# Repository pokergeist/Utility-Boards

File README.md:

# Utility-Boards
Printed curcuit boards designs and associated code for hobby and task related PCBs.

### [Power Alert](Power_Alert/README.md)

An Adafruit Itsy Bitsy powered board that alarms when the power goes out. Extended with an I2C Qwiic connector and pin access for projects that could use batter power (with charging) or big LED or Piezo speaker.

### Pending

I created a few printed circuit boards to perform some simple tasks. Pending uploads:
  * Lighting - using motion sensing to control 12V LED strips (single-color or RGB). Used for under-counter task lighting (color fades to full white) and walkway lighting (on/off).
  * Power Alert - generate an alert (flashing LED and Piezo speaker) when USB or 5V power to the board is lost. It continues to blink after power is restored as a notification. A Li-Po battery provides backup power and is recharged by the board when power is restored.
  * Heater control - string multiple temperature sensors together with phone wire to control a heater. Used in outbuildings to prevent plumbing and fixtures from freezing.

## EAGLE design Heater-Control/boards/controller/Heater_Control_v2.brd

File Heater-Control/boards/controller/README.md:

# Heater Controller Board

## Introduction

This project uses a microcontroller to read a chain of Dallas Semiconductor DS18B20 1-Wire temperature sensors. When any of the sensors reads too low an electric heater is turned on via a "IOT" Power Strip which has a low voltage trigger input (not some Wi-Fi silliness).

The sensors boards are connected together with cheap phone wire cords with RJ-11 connectors on the ends. The control line to the power strip connects via a JST XH 2-pin connector to the strip's screw terminal block, which is removable for easier connection.

The sensor boards have been used with an Arduino Uno and protoboard shield to prevent plumbing and fixtures in an outbuilding from freezing for a few seasons now. This is the next generation build that uses a custom (but simple) circuit board with a smaller enclosure, simpler wiring, and a display.

## Status

|    Date    | Status                                                       |
| :--------: | ------------------------------------------------------------ |
| 2022-24-23 | Added strong pull-up MOSFET and changed pull-up resistor.    |
| 2022-12-18 | Adding a strong pull-up for the DQ line as stability problems have been encountered. |
| 2022-12-02 | First check-in. Gerber and software files pending.           |

**2022-12-23** Reliability Issues have been resolved by reducing the pullup-up resistor value to 3.3k to maintain 1mA of current. The strong pull-up MOSFET didn't resolve the issue, but won't hurt for longer runs, and is deemed a required component in the DS18B20 datasheet. The MOSFET is turned on to sort-of fast charge the sensors before certain operations.

**2022-12-18** One unit has worked fine, the other will either not recognize connected sensors, or the sensors do not stay on-line. The driver supports a strong pull-up provided by a P-channel MOSFET driven by a second GPIO line.

Moving from a 5V MCU to a 3.3V one has probably exposed a lurking problem if the datasheet is any indication.

## Parts List

| Part                        |                            Part #                            |     Quantity      |       Price @q1       | Notes                                                        |
| --------------------------- | :----------------------------------------------------------: | :---------------: | :-------------------: | ------------------------------------------------------------ |
| Microcontroller             | Adafruit QT Py SAMD21 (#[4600](https://www.adafruit.com/product/4600)) [D-K](https://www.digikey.com/short/z7fjv1m0) |         1         |         $7.50         | Available on Digi-Key too.                                   |
| P-Ch MOSFET                 | Microchip [TP2104N3-G](https://www.digikey.com/short/nzjn4r47) |         1         |         $0.74         |                                                              |
| RJ-11 Jack                  |       [43860](https://www.digikey.com/short/1ht3wp4m)        |      1 or 2       |         $1.15         | Combine w/ sensor boards for pricing.                        |
| JST XH-2                    |  [S2B-XH-A(LF)(SN)](https://www.digikey.com/short/hw1pfpn8)  |         1         |         $0.16         |                                                              |
| 3.3kΩ 1206 resistor         | Stackpole [RMCF1206JT4K70](https://www.digikey.com/short/4qf3n4vb) |         1         |         $0.10         | (10) @ $0.025 each                                           |
| 100Ω 1206 resistor          | Stackpole [RMCF1206JT100R](https://www.digikey.com/short/2cb7z251) |         1         |         $0.10         | (10) @ $0.025 each                                           |
| OLED display                |                   SSD-1306 128x32 4-lines                    |         1         |           ?           | Amazon or eBay                                               |
| Qwiic/SQT cable             |                 4-conductor w/ JST connector                 |         1         |           ?           | Amazon or eBay                                               |
| "IOT" Power Strip           |   Adafruit #[2935](https://www.adafruit.com/product/2935)    |         1         |        $34.95         |                                                              |
| PCB                         |           Zipped Gerber files for JLCPCB or PCBWay           |         1         | (5) for $2 + shipping | Shipping speed is the biggest cost factor.                   |
| 4-conductor telephone cable |                          RJ-11 6p4c                          | 1 for each sensor |           ?           | Must be 4-conductor in concentric pairs. The outer two positions of a 6p4c connector are not used. |

## Component Functions

The  microcontroller reads the sensors and controls the power strip. It also displays information to the optional OLED display and/or LED/Neopixel.

The Molex RJ-11 jack connects to the sensor line via 4-conductor telephone cables.

The JST XH 2-pin connector connects to the power strip to turn it on and off.

The pull-up resistor pulls the DQ 1-wire data line up to 3V3. The MOSFET provides a strong pullup-up to 3V3 prior to certain operations. The driver is responsible for not setting the DQ line LOW at the same time.

The optional 128x32 pixel 4-line I2C OLED display show individual and minimum temperatures per read cycle, the lowest long-term temp, heater status, and total heater run-time. Or whatever you care to add to the code.

The Qwiic/STEMMA QT cable provide power and data to the OLED display. Order a short cable and solder one end to the display, and plug the connector end into the QT Py micro.

## Board Images

## Wiring

Power is provided via a USB-C cable to the QT Py micro. The small heater is powered from the power strip which also power the USB-C cable via one of the "Always On" outlets.

The OLED display is controlled and powered via the Qwiic/STEMMA QT I2C connector on the QT Py micro.

When using cheap 4-conductor phone line line you'll find that the the connectors are often crimped such that the pin order is reversed from end-to-end. This is not an issue for phone equipment using the outer and inner concentric pairs. You do have to make sure that it's a 4-conductor cable and not just 2 conductors for the center pair.

The DS18B20 supports parasitic power. The three terminals are:

* Vdd - power
* DQ - data
* GND - ground

With power provided via the pulled-up DQ line, and the Vdd pin grounded, the IC operates on parasitic power. I use both leads of the inner pair for data/power line DQ and the outer pair for ground.

## The Enclosure

The SCAD and .stl files for a simple enclosure are provided. (still tweaking the design)

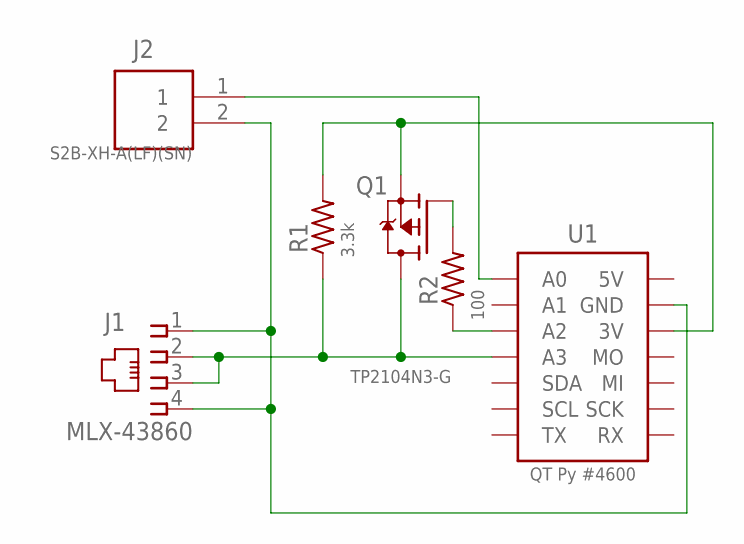
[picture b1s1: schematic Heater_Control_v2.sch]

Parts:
J1: MLX-43860
J2: S2B-XH-A(LF)(SN); HDR-02/RA
Q1: TP2104N3-G; TO92-
R1: 3.3k; R1206
R2: 100; R1206
U1: QT Py #4600; QT_PY-TH

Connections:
3V3: Q1.1 (S), R1.2, U1.3V3@1 (3V), U1.3V3@2 (3V)
5V: U1.5V@1 (5V), U1.5V@2 (5V)
DATA-1WIRE: J1.2, J1.3, Q1.3 (D), R1.1, U1.A3@1 (A3), U1.A3@2 (A3)
GATE: Q1.2 (G), R2.2
GND: J1.1, J1.4, J2.2, U1.GND@1 (GND), U1.GND@2 (GND)
PWR: J2.1, U1.A0@1 (A0), U1.A0@2 (A0)
SPU_GATE: R2.1, U1.A2@1 (A2), U1.A2@2 (A2)

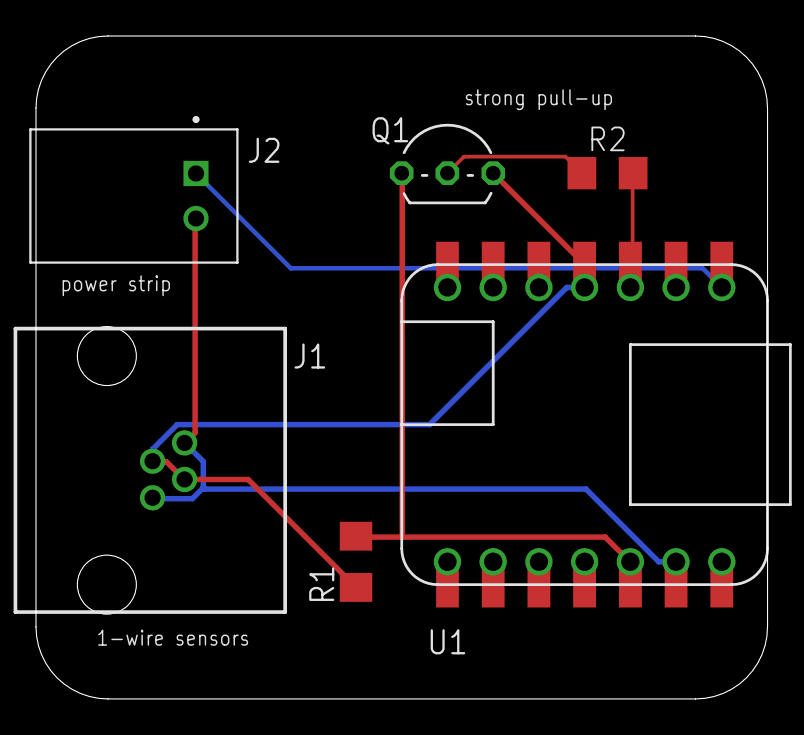
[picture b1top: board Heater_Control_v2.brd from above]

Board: 2 copper layers, 40.6 x 36.8 mm, 6 parts (0 on the bottom side), 7 nets.

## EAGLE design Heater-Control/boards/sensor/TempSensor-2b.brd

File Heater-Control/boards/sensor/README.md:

# Heater Sensor Board

## Intro

This project uses a microcontroller to read a chain of Dallas Semiconductor DS18x20 1-Wire temperature sensors. When any of the sensors reads too low an electric heater is turned on via a "IOT" Power Strip.

The sensors boards are connected together with cheap phone wire cords with RJ-11 connectors on the ends. The control line to the power strip connects via a JST XH 2-pin connector to the strip's screw terminal block, which is removable for easier connection.

The sensor boards have been used with an Arduino Uno and protoboard shield to prevent plumbing and fixtures in an outbuilding from freezing for a few seasons now. This is the next generation build that uses a custom (but simple) circuit board with a smaller enclosure, simpler wiring, and a display.

## Status

|    Date    | Status                                           |
| :--------: | ------------------------------------------------ |
| 2022-12-03 | Redesigned Sensor board. Ordered (5) 3x3 panels. |
| 2022-12-02 | First check-in. Gerber files are pending.        |

As fate would have it I need more sensor boards so I revised the sensor part schematic then the board. Obsolete parts were removed. Mounting options were revised.

## Parts List

|        Item        |                         Part #                          | Quantity |                     Price @q10                      | Notes                                      |
| :----------------: | :-----------------------------------------------------: | :------: | :-------------------------------------------------: | ------------------------------------------ |
| Temperature Sensor | [1-Wire Search](https://www.digikey.com/short/5w14dwnw) |    1     |                       $6.413                        | See below.                                 |
|     RJ-11 Jack     |     [43860](https://www.digikey.com/short/1ht3wp4m)     |  1 or 2  |                       $0.949                        |                                            |
|        PCB         |        Zipped Gerber files for JLCPCB or PCBWay         |    5+    | (5) for $2 + shipping<br/>(45) for $7.30 + shipping | Shipping speed is the biggest cost factor. |

**Notes on the PCB:**

The new PCB is small enough to be panelized where multiple boards are made on one panel and milled so that they snap apart. The standard minimum order is (5) 100x100mm (or smaller) boards for $2.00 plus shipping. With panelized boards you get (5) panels for a few dollars more. With (9) boards per panel you can easily get (45) individual boards for a reasonable price.

**Notes regarding the temperature sensor:**

The old Dallas Semi DS18x20 1-Wire Temperature sensor has fallen out of favor and is becoming increasingly rare and costly. Items to consider regarding the Digi-Key search results linked to above:

* The MAX31820  sensors are cheaper but the DS18(b)20/20 has better accuracy from +10°C to -10°C.
* These offer 11 or 12-bit precision - I'm only using 10-bits.

You can probably source the DS18B20 sensors cheaper on eBay or [AllElectronics.com](https://www.allelectronics.com/item/ds18b20/digital-temperature-sensor/1.html).

After my stock of DS18B20s runs out I'll probably switch to a cheap I2C-based chip, but that would ruin my scheme of using cheap phone cables without regard to their connector polarity (which was a pain to check on every single cable).

## Wiring

When using cheap 4-conductor phone line line you'll find that the the connectors are often crimped such that the pin order is reversed from end-to-end. This is not an issue for telephone equipment using the outer and inner concentric pairs. You do have to make sure that it's a 4-conductor cable and not just 2 conductors using only the center pair.

The DS18x20 supports parasitic power. The three terminals are:

* Vdd - power
* DQ - data
* GND - ground

With power provided via the pulled-up DQ line, and the Vdd pin grounded, the IC operates on parasitic power. I use both leads of the inner pair for data/power line DQ and the outer pair for ground.

## Mounting Options

The new board offers multiple mounting options:

* There are notches for mounting with a cable tie.
* Two M3 holes are provided at the center and corner.
* A sensor can be soldered on either side (or even both sides if desired).

## Schematic

The schematic shows two locations for the sensor, U1T and B for top and bottom. This gives the option of installing a sensor **on either the top or bottom side** depending on how the board is mounted and the best location for the sensor. You could install two sensors, but that is not the intention.

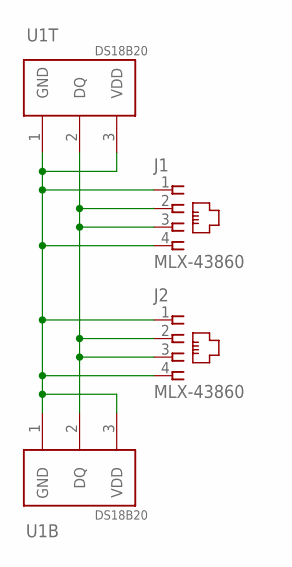
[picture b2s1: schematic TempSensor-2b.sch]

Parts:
J1, J2: MLX-43860
U1B, U1T: DS18B20; TO92-

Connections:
1W: J1.2, J1.3, J2.2, J2.3, U1B.2 (DQ), U1T.2 (DQ)
GND: J1.1, J1.4, J2.1, J2.4, U1B.1 (GND), U1B.3 (VDD), U1T.1 (GND), U1T.3 (VDD)

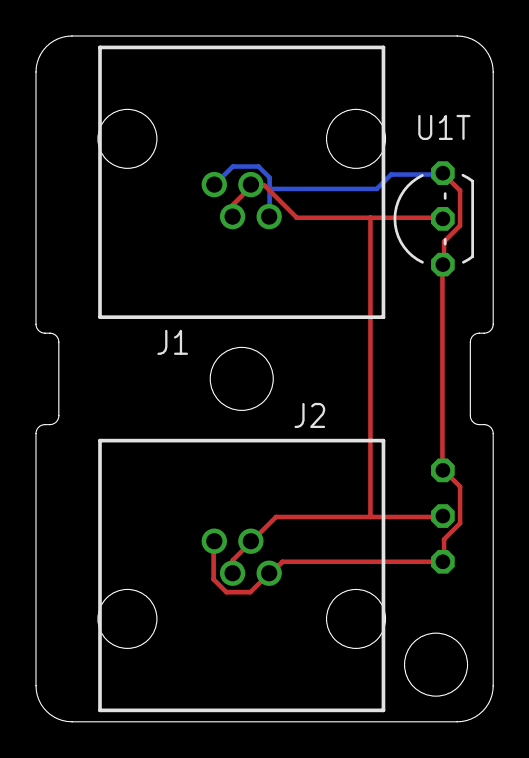
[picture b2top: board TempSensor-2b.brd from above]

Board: 2 copper layers, 25.4 x 38.1 mm, 4 parts (1 on the bottom side), 2 nets.

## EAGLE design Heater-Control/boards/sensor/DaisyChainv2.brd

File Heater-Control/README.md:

# Heater Control Project

## Intro

This project uses a microcontroller to read a chain of Dallas Semiconductor DS18B20 1-Wire temperature sensors. When any of the sensors reads too low an electric heater is turned on via a "IOT" Power Strip.

The sensors boards are connected together with cheap phone wire cords with RJ-11 connectors on the ends. The control line to the power strip connects via a JST XH 2-pin connector to the strip's screw terminal block, which is removable for easier connection.

The sensor boards have been used with an Arduino Uno and protoboard shield to prevent plumbing and fixtures in an outbuilding from freezing for a few seasons now. This is the next generation build that uses a custom (but simple) circuit board with a smaller enclosure, simpler wiring, and a display.

## Status

|    Date    | Status                                                       |
| :--------: | ------------------------------------------------------------ |
| 2022-12-24 | Updated control board files.                                 |
| 2022-12-23 | Changed out the 4.7kΩ pull-up resistor for a 3.3kΩ one and finished the installation. |
| 2022-12-18 | Adding a hard pull-up for the DQ line as stability problems have been encountered. |
| 2022-12-02 | First check-in. Gerber, enclosure, and software files pending. |

**2022-12-23** I added the p-channel MOSFET for the strong pull-up. That didn't improve anything at all. I finally swapped out the 4.7kΩ pull-up resistor for a 3.3kΩ one since the voltage had changed from 5V to 3.3V. After that the project started working reliably with and without the strong pull-up function. I'll be adding the strong pull-up components to the board design - it will likely help with longer sensor runs.

**2022-12-18** One unit has worked fine, the other will either not recognize connected sensors, or the sensors do not stay on-line. The driver supports a hard pull-up provided by a P-channel MOSFET driven by a second GPIO line.

Moving from a 5V MCU to a 3.3V one has probably exposed a lurking problem if the datasheet is any indication.

## The Boards

### The Controller Board

The controller board hosts:

*  an Adafruit QT Py SAMD21 (#4600) microcontroller
* a Molex RJ-11 jack for connecting to the sensor line
* a JST XH 2-pin connector for controlling the power strip
* a pull-up resistor to pull the DQ 1-wire data line up to 3V3
* an optional 128x32 pixel 4-line I2C OLED display.

### The Sensor Board

Sensor board components:

* A Dallas Semi DS18B20 1-Wire Temperature sensor
* a Molex RJ-11 Jack
* Deprecated components:
  * a JST XH 3-pin for connecting to the old controller (now vacant)
  * a 4.7kΩ pull-up resistor for use with the old controller (now vacant)

## Wiring

When using cheap 4-conductor phone line line you'll find that the the connectors are often crimped such that the pin order is reversed from end-to-end. This is not an issue for phone equipment using the outer and inner concentric pairs. You do have to make sure that it's a 4-conductor cable and not just 2 conductors for the center pair.

The DS18x20 supports parasitic power. The three terminals are:

* Vdd - power
* DQ - data
* GND - ground

With power provided via the pulled-up DQ line, and the Vdd pin grounded, the IC operates on parasitic power. I use both leads of the inner pair for data/power line DQ and the outer pair for ground.

Power is provided via a USB-C cable to the QT Py micro. The small heater is powered from the power strip which also power the USB-C cable via one of the "Always On" outlets.

The OLED display is controlled and powered via the Qwiic/STEMMA QT I2C connector on the QT Py micro.

## The Enclosure

The SCAD and .stl files for a simple enclosure are provided. (still tweaking the design)

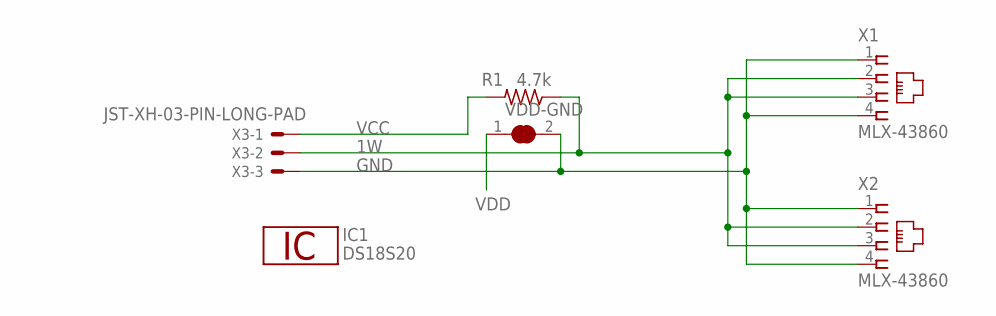
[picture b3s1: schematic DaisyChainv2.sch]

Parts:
IC1: DS18S20; TO92-
R1: 4.7k; 0207/10
VDD-GND: SJW-SHORTED
X1, X2: MLX-43860
X3: JST-XH-03-PIN-LONG-PAD; JST-XH-03-PACKAGE-LONG-PAD

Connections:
1W: IC1.2 (1W), R1.1, X1.2, X1.3, X2.2, X2.3, X3.2
GND: IC1.1 (GND), VDD-GND.2, X1.1, X1.4, X2.1, X2.4, X3.3
VCC: R1.2, X3.1
VDD: IC1.3 (VDD), VDD-GND.1

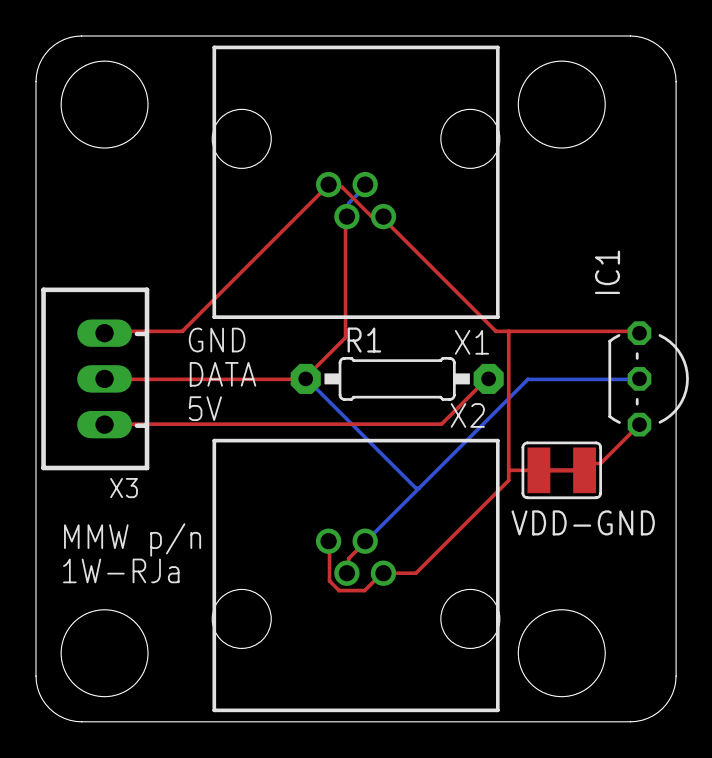
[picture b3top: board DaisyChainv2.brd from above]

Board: 2 copper layers, 35.6 x 38.1 mm, 6 parts (0 on the bottom side), 4 nets.

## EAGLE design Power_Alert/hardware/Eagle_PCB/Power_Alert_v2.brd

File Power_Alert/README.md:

# Power Alert

A board that alerts you to a power loss. Maybe more.

### Overview

This board has some general utility given that it has:

+ a big, bright LED
+ a Piezo speaker
+ a battery connector for a lithium battery - Li-ion or Li-po pouch cell
+ a charging IC for the lithium battery (4.2V).

To that end it has been extended for alternate uses. It provides:

* a Qwiic/STEMMA QT I2C connector providing GND, V+, SDA and SCL for connection to sensors, displays, ...
* exposed Itsy Bitsy MCU pins
  * GPIO: A0, A1,  A2, D4, D6, D8
  * SPI: MOSI, MISO, SCLK
  * Power: Vdd, GND

### Board Components

An export of my [Digi-Key](https://www.digikey.com/) project list is located in the hardware folder. Two things to be aware of:

1. Two piezo elements are listed. The [larger](https://www.digikey.com/en/products/detail/tdk-corporation/PS1740P02E/935933) diameter one is shorter and has better specs and is preferred. A [second](https://www.digikey.com/en/products/detail/tdk-corporation/PS1420P02CT/935925) one is listed as an alternate.
2. The current limiting resistor (R5) was selected based on the LED I had on hand (Vf 1.67V) for 20mA current. It's a bit bright - a higher value for less current and power may be desirable.
3. There is no LED in the list because I used what I had in stock (p/n unknown). Pick something similar and pick an appropriate current limiting resistor. All resistors are SMD 1206 size.

#### MCU

An Adafruit ItsyBitsy 32u4 3V 8MHz microcontroller board, product [#3675](https://www.adafruit.com/product/3675) is used given that it will run off of a Li-po cell and is reasonably priced (~$9.95). Please be aware that pin assignments vary on different versions of the Itsy Bitsy form factor board.

##### Pins Used

MCU pins are:

* Power: BAT, USB, 3V3, GND
* Outputs:
  * 11 - Piezo Alert, PWM
  * 10 - LED Alert, active low, low-side switch (switched to ground)
  * 13 - LED_BUILTIN used to indicate that battery charging is in progress
* Inputs:
  * 12 - Voltage divider - ADC sensing of Vin (Vusb or Vbat) / 2
  * 7 - Charge Status, active low when charging
* Other pins exposed as mentioned above.

#### Lithium Cell Charger

The Microchip [MCP73832T](https://www.digikey.com/short/nh2n5n3z) is currently out of stock so please check the product page before proceeding - if you care about battery charging that is.

#### Piezo Element

The piezo speaker supports variable frequencies using a modulated output. Here I use 50% pulse width modulation (PWM) via the tone() function.

#### Discrete Components

* Bypass capacitors C1 & C2 are for the charger IC.
* Resistors R1 & R2 form the voltage divider used for voltage sensing.
* R3 is the recommended value for use with the piezo element.
* R4 sets the charging voltage (or maybe the current) .
* R5 limits the current and provides the appropriate voltage for LED1.
* LED1 is your typical 5mm LED, unspecified otherwise.

### The Battery

I used a flat lithium Li-po pouch cell that fits well behind the board. I have not measured power consumption while the board is alerting, but I suspect the will last well over a day.

The battery is terminated with a JST XH 2-conductor connector. **Please note the polarity of the red and black leads!** There is no standard convention that you can rely on. The polarity is marked on the board such that the red lead is toward the MCU.

The cell should be fitted with a DW-01 type **protection circuit** that prevents overcharging, over-discharging, and over-current conditions. The circuit is usually mounted on top under the Kapton polyamide tape.

### Mounting

The board can be mounted using (4) M3 screws or the flanges on the top an bottom of the board.

### Software

The provided code is just for my application. Feel free to tinker.

The board is expected to be powered with 5V via the micro-USB cable.

#### Board Operation

##### Power-up

On power-up the MCU turns on the beeper and LEDs twice to indicate that the alerting components are functioning.

##### Running Normally

 If the charging IC senses that the battery needs charging the MCU will sense that and turn on the small LED on the microcontroller board.

There will be a very short pulse of the big LED once a second to indicate that the board is functioning and that there have been no power losses.

##### Loss of USB Power

Upon loss of USB power the board will start beeping and flashing. **To turn off the !^$# beeping**, press the RESET button on the MCU.

##### Restoration of Power

When USB power is restored, beeping will stop, but the LED will continue to flash an alerting pattern to indicate an earlier power loss. Press the MCU's reset button to reset this indication.

### Images

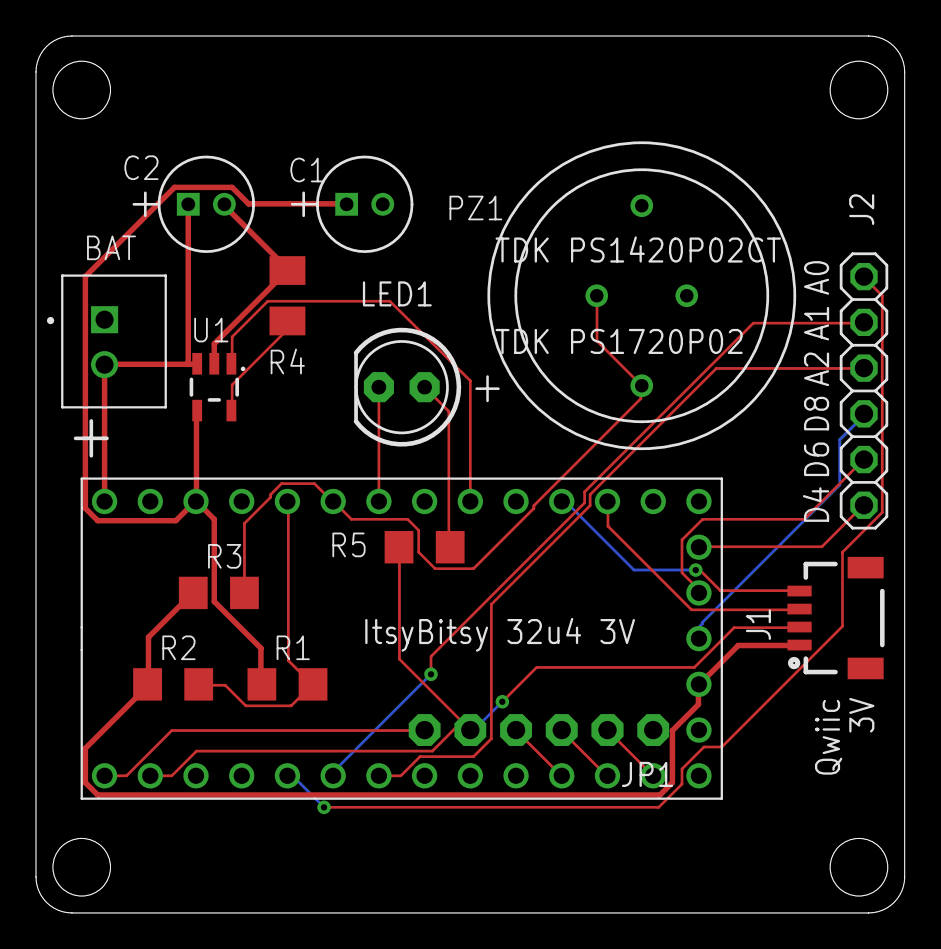
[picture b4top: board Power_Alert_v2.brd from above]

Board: 2 copper layers, 48.3 x 48.7 mm, 16 parts (0 on the bottom side), 22 nets.

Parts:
BAT: B2B-XH-A(LF)(SN)
C1, C2: 47uF; CAP-RADIAL-2X5
J1: 1X04_1MM_RA
J2: 1X06
JP1: 1X06-CLEANBIG
LED1: LED5MM
PZ1: TDK-PS1420P02CT
PZ1B: TDK-PS1720P02
R1, R2: 2.7k; R1206
R3: 1k; R1206
R4: 2k; M1206
R5: 65; R1206
U1: MCP73831; SOT23-5
U2: ItsyBitsy 32u4 3V; ITSYBITYS-32U4

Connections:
3V3: J1.2, JP1.5, R5.2, U2.P$2
!CHARGE_STATUS: U1.1, U2.P$25
A0: J2.6, U2.P$5
A1: J2.5, U2.P$6
A2: J2.4, U2.P$7
ALERT: PZ1.P$1, PZ1B.P$1, R3.1, U2.P$28
BAT: BAT.2, C2.1, U1.3, U2.P$33
D4: J2.1, U2.P$19
D6: J2.2, U2.P$18
D8: J2.3, U2.P$17
GND: BAT.1, C1.2, C2.2, J1.1, JP1.1, PZ1.P$2, PZ1B.P$2, R2.1, R3.2, R4.2, U1.2, U2.P$14, U2.P$16, U2.P$32
LED_EXT: LED1.K, U2.P$27
MISO: JP1.2, U2.P$13
MOSI: JP1.3, U2.P$12
unnamed: LED1.A, R5.1
PROG: R4.1, U1.5
RST: JP1.6, U2.P$1
SCK: JP1.4, U2.P$11
SCL: J1.4, U2.P$23
SDA: J1.3, U2.P$22
SENSE: R1.1, R2.2, U2.P$29
USB: C1.1, R1.2, U1.4, U2.P$31

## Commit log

2022-04-19 repo startup
2022-04-23 first ci
2022-04-23 added BAT header
2022-04-23 moved schematic image
2022-04-23 readme typo
2022-04-23 IB pinout warning
2022-04-24 link to PwrAlert
2022-04-24 assembled image
2022-04-24 rm BIG img
2022-12-02 enclosure
2022-12-02 enclosure update
2022-12-03 Heater Control
2022-12-03 board readme files
2022-12-03 new sensor board
2022-12-03 reorg
2022-12-03 +controller Gerber file
2022-12-03 sensor bd status & pricing
2022-12-19 issue++
2022-12-23 the fix
2022-12-24 updated control board
2022-12-24 typo
2022-12-24 control board images
2022-12-24 sensor board readme update

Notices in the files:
parts and their libraries:
SparkFun-IC-Power: Licensing: Creative Commons ShareAlike 4.0 International - https://creativecommons.org/licenses/by-sa/4.0
